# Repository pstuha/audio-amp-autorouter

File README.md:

# AmpRoute Studio 2.2.0

**Agent-first autorouter and 2-D board editor for LUT audio-amplifier PCBs.**

An AI agent invents a circuit and describes a board; AmpRoute turns it into a
DRC-clean, manufacturable PCB with Gerbers, a 1:1 toner-transfer template and
official CAM files. A human opens the same board in a familiar KiCad-like
editor. No KiCad plugin, no Python runtime, no external services.

---

## 60-second start

```powershell
cargo build --release           # target\release\amproute-studio.exe
.\target\release\amproute-studio.exe
```

GUI: **Open board…** → pick `.kicad_pcb` or JSON → **F5** → choose
**Export folder…** → **Ctrl+E**. No board is preloaded: the shipped amplifiers
are test fixtures, not presets.

Headless:

```powershell
# Route one of the five shipped test boards
.\amproute-studio.exe --cli --board lm386-mini -o out --json

# Route an agent-designed board
.\amproute-studio.exe --cli -i my_board.json -o out --json

# Two-layer variant with plated vias
.\amproute-studio.exe --cli -i my_board.json --two-layer -o out2 --json

# Official CAM formats (from KiCad's own exporters)
.\amproute-studio.exe --cli -i my_board.json --odb --ipc -o cam

# Machine-readable agent interface
cargo build --release --bin amproute-mcp
```

Exit codes: `0` success, `2` invalid board, `3` routing/export refused.

---

## What it does

| Stage | Implementation |
|-------|----------------|
| **Import** | `.kicad_pcb` and AmpRoute JSON; rotates footprints correctly; reports every skipped KiCad feature. |
| **Rules** | `R01`–`R11`: LUT feature band, vias, width, clearance, net class, acute corners, parallel runs, annular ring, drill, edge clearance. |
| **Placement** | Opt-in 180° footprint optimizer (`--optimize-placement`, MCP `optimize_placement`). |
| **Routing** | 8-connected/octile A* with exact-mm `Occupancy`, audio proximity penalties, star-ground and thermal zones, rip-up/reroute, line-of-sight simplification, 45° canonicalisation and LUT width taper. |
| **Verification** | Own audit + `kicad-cli pcb drc --severity-all`; 15 reference boards at 100 % routing with zero violations. |
| **Quality** | DC drop, I²R, IPC-2221 width, linear AC (MNA), EMI/crosstalk proxies, transient thermal — all versioned JSON. |
| **Export** | Gerber, SVG, PDF, 1:1 LUT template (front and mirrored back), `.kicad_pcb`, Excellon drill, IPC-2581 Rev C, ODB++ zip. |
| **Agents** | CLI `--json` (one document on stdout) and MCP JSON-RPC 2.0 over stdio. |

### Agent workflow

1. Agent creates a board (JSON or `.kicad_pcb`) — no GUI needed.
2. `route_board` validates, routes, audits and writes every deliverable.
3. `get_result` returns nets, DRC, measurements, quality verdict and exact file paths.
4. Human prints `lut_print.pdf` at 100 %, transfers toner, etches and solders.

Ten agent-designed boards are built in (`pam8403-mini`, `lm358-preamp`,
`tda2822-bridge`, `ne555-tone`, `classa-single`, `jfet-buffer`,
`discrete-opamp`, `lm1875-mono`, `ta2024-tripath`, `hybrid-output`) alongside
five shipped fixtures (`lm386-mini`, `tda2030-compact`, `cmoy-headphone`,
`classic-ltp`, `twin-pair-200`). All 15 route 100 % with KiCad DRC clean.

### Audio-specific routing

- Net classes set width, priority and routing cost (GND/PWR first, sensitive
  inputs short and direct).
- Input↔Power/Output proximity penalty ×10; Feedback↔Output/Power ×5.
- Star-ground bias (`board.rs::star_ground_point`) and thermal hotspot keep-outs.
- Single-layer LUT by default: vias forbidden, insulated-wire jumpers instead.
- Two-layer mode adds plated vias, B.Cu Gerber, mirrored B.Cu LUT sheet and drill.

---

## GUI

Familiar EDA layout: menu bar, toolbars, appearance/net/component tree, board
canvas, inspector, DRC and statistics, status bar.

- Zoom with the wheel, pan by drag, rotate with `R`/`Shift+R`, mirror with `F`.
- Click a pad, track, component or net to inspect it.
- Toggle layers, keep-outs and thermal heatmap.
- Statistics: board totals (copper, segments, routed nets), track-width min / avg / max,
  per-net table and thermal peak / average — **Copy stats** copies it to the clipboard.
- `F5` route, `Esc` stop, `Ctrl+O` open, `Ctrl+K` KiCad export, `Ctrl+E` all exports.
- Routing runs on a worker thread — the UI stays responsive.

---

## Machine interface

CLI `--json` prints exactly one `PipelineResult` JSON document; diagnostics go
to stderr. MCP server:

| Tool | Purpose |
|------|---------|
| `get_capabilities`, `get_quality_schema` | API version, formats, analysis schema |
| `list_boards`, `list_extra_boards` | Fixtures and agent designs |
| `validate_board`, `run_drc` | Pre-flight checks |
| `route_board`, `get_result` | Route, export and retrieve the full report |
| `run_ac`, `generate_netlist`, `run_emi`, `run_thermal` | Proxy analyses |
| `optimize_placement`, `set_lut_profile`, `suggest_jumpers` | Agent helpers |

Full contract: [`docs/agent-api.md`](docs/agent-api.md).

### Quality verdict

`quality` is separate from manufacturability. Hard gates: all nets routed,
rules clean, own DRC clean, KiCad DRC clean, exports written. Electrical,
AC, EMI and thermal verdicts gate `ok` only when the agent supplies data and
selects them through `analysis_policy`. All proxy reports carry `model`,
`confidence` and `assumptions`.

Honest verdicts: while currents are **assumed** (`assumed_currents: true`),
electrical violations (M02 track width vs IPC-2221, M03 drop) are advisory;
with real agent-supplied currents (`measure_currents`, `NetExcitation`) the
same violations gate `ok`. `assumed_currents: false` in every `get_result`.

History and comparisons: [`docs/quality-roadmap.md`](docs/quality-roadmap.md),
[`docs/router-roadmap.md`](docs/router-roadmap.md).

---

## Output files

| File | Purpose |
|------|---------|
| `board.gbr`, `board_b.gbr` | RS-274X copper layers, 4.6 format, millimetres |
| `board.svg` | Colour preview |
| `board.pdf` | Route report |
| `lut_print.pdf`, `lut_print_b.pdf` | 1:1 iron-on templates, front/mirrored back — print at 100 % |
| `<board>.kicad_pcb` | KiCad project board |
| `vias.drl` | Excellon drill for plated vias |
| `jumpers.csv` | Insulated-wire jumper endpoints |
| `board.xml` | IPC-2581 Rev C (KiCad exporter) |
| `board_odb.zip` | ODB++ (KiCad exporter) |

---

## Verification

```text
cargo test — 248 tests, 0 failures:
  215 unit + 5-board acceptance + 10-board acceptance
  e2e, MCP, reference, quality, standards, two-layer, SPICE golden

scripts\bench_validate.ps1 — routes all 15 boards, checks result.ok = true

kicad-cli pcb drc --severity-all   # 0 violations on all 15 boards
lm386-mini: 7/7 nets, non_canonical segments = 0
```

The golden SPICE test runs only when `AMPROUTE_NGSPICE` points to a simulator;
otherwise it skips. KiCad 10 is used automatically for DRC and optional CAM.

---

## Project layout

```
src/
  agent.rs, bin/amproute-mcp.rs   MCP/JSON agent interface
  board.rs, boards.rs             Model, net classes, fixtures and agent designs
  import.rs, sexpr.rs, kicad.rs   KiCad round-trip
  router.rs, routing_engine.rs    A*, octile search, rip-up, canonicalisation
  occupancy.rs, two_layer.rs      Exact clearance, layered completion
  preroute.rs, jumper.rs          Star power/ground, insulated-wire jumpers
  rules.rs, drc.rs                LUT rules and DRC
  measure.rs, ac.rs, emi.rs       DC/AC/EMI quality proxies
  thermal.rs                      2-D conduction + transient estimate
  export.rs                       Gerber/SVG/PDF/LUT/CAM
  gui.rs, main.rs                 egui editor and CLI
tests/                             Acceptance and contract tests
docs/                               Agent API and roadmaps
```

---

## Limitations

- Through-hole only; two-layer vias are supported in the tool but require a
  manufactured two-layer board.
- KiCad import is deliberately partial (no zones, teardrops or custom pads);
  skipped features are reported.
- Thermal is a 2-D/RC proxy, AC is linear MNA, EMI is geometric — none is a
  full-wave or FEM solver.
- Always verify scale/orientation in an independent Gerber viewer before fab.

---

## Bench validation

`scripts\bench_validate.ps1` routes all 15 boards and checks `result.ok`
(routability smoke — also used in CI).

**Bench validation of an amplifier is blocked — no physical bench is available
in this environment.** When a bench is available, the full procedure is:

1. **Routability smoke** — `scripts\bench_validate.ps1`: every board must print
   `OK` and exit 0. Reference: `lm386-mini` → 4 files, `drc=0`, `kicad_drc_ran=true`.
2. **Gain** — feed a 1 kHz sine (~0.1–1 Vpp) through the board's normal signal
   path (input pin → front-end net → output pad) with a function generator and
   a scope; compare with the board's class gain (net classes in the board JSON).
3. **THD** — same path, measured with a spectrum/FFT analyzer at a few levels
   (e.g., 0.1 / 1.0 × supply max); record %THD vs the class spec.
4. **Temperature** — run the board at max supply/output for a few minutes;
   measure with an IR camera or thermistor taps on the copper; keep the
   junction rise within the model's thermal limits.

Bench results become part of the record via `measure_currents` (then they
gate `ok`) or explicit `analysis_policy` — see
[`docs/agent-api.md`](docs/agent-api.md).

## Building

Rust 1.75+. On Linux install `libxkbcommon`, `libwayland-dev`, `libgl1-mesa-dev`.

```bash
cargo build --release
cargo test
```

## License

MIT — see [LICENSE](LICENSE).

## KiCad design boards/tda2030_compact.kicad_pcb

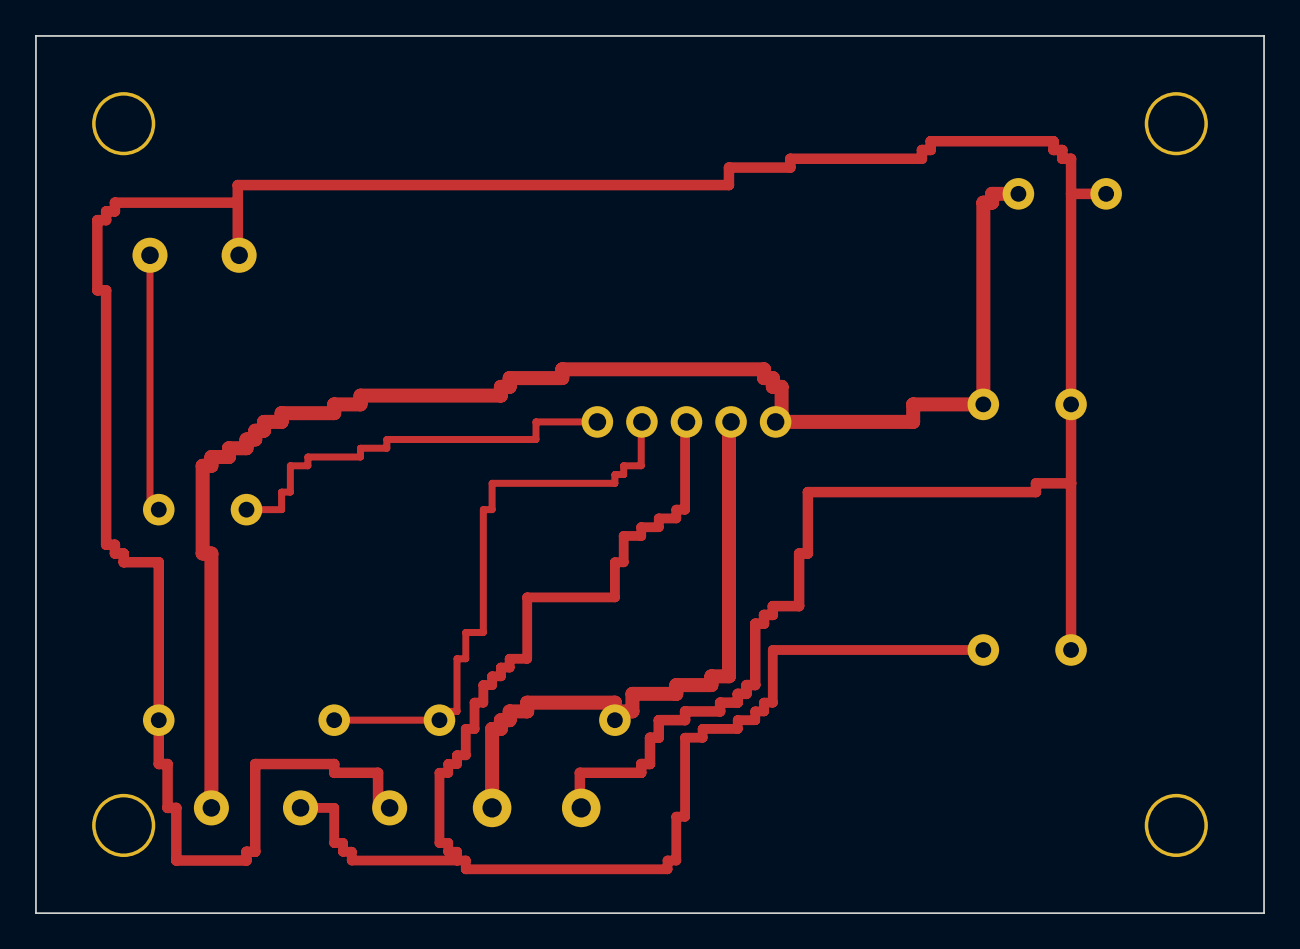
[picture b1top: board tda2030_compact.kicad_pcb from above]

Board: 2 copper layers, 70.0 x 50.0 mm, 14 parts (0 on the bottom side), 7 nets.

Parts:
C1: 2u2
C2: 100nF
C3, C4: 2200uF
H1, H2, H3, H4: MountingHole; MountingHole_3.2mm
J1: RCA-IN
J2: PWR
J3: SPK
R1: 22k
R2: 680R
U1: TDA2030

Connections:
FB: R1.1, R2.2, U1.2
GND: C2.2, C3.2, C4.2, J1.2, J2.3, J3.2, R2.1
IN: C1.1, J1.1
IN_AC: C1.2, U1.1
OUT: J3.1, R1.2, U1.4
V+: C2.1, C3.1, J2.1, U1.5
V-: C4.1, J2.2, U1.3

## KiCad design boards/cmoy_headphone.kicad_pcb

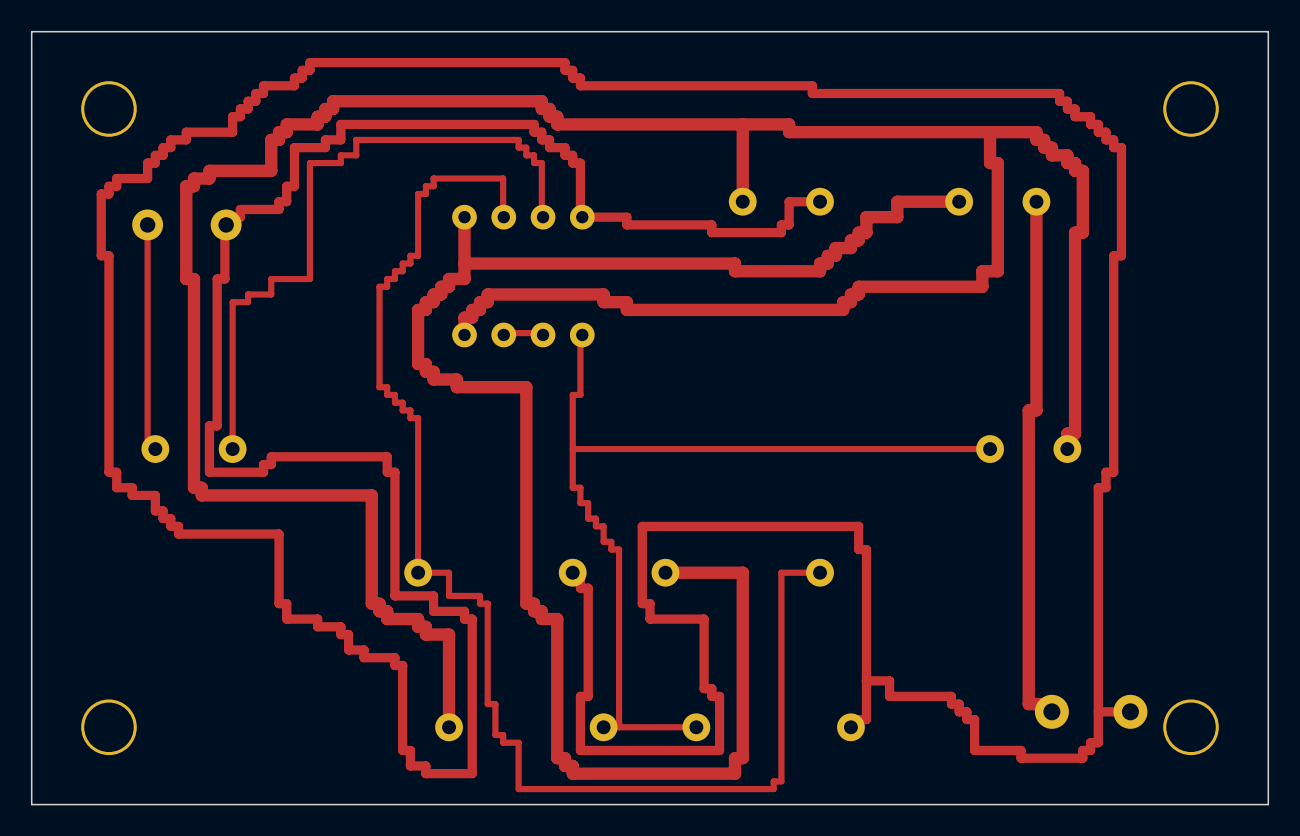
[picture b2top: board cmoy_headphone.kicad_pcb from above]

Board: 2 copper layers, 80.0 x 50.0 mm, 15 parts (0 on the bottom side), 9 nets.

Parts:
C1: 1uF
C2: 470uF
C3: 100uF
C4: 10uF
H1, H2, H3, H4: MountingHole; MountingHole_3.2mm
J1: RCA-IN
J2: SPK
R1, R3, R4: 10k
R2: 47k
U1: NE5532

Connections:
AMP_OUT: C2.1, R2.1, U1.1
FB: R1.1, R2.2, U1.2
GND: C4.2, J1.2, J2.2, R1.2, R4.2, U1.4
IN: C1.1, J1.1
IN_AC: C1.2, U1.3
PHONES: C2.2, J2.1
SPARE: U1.6, U1.7
V+: C3.2, C4.1, R3.1, U1.8
VGND: C3.1, R3.2, R4.1, U1.5

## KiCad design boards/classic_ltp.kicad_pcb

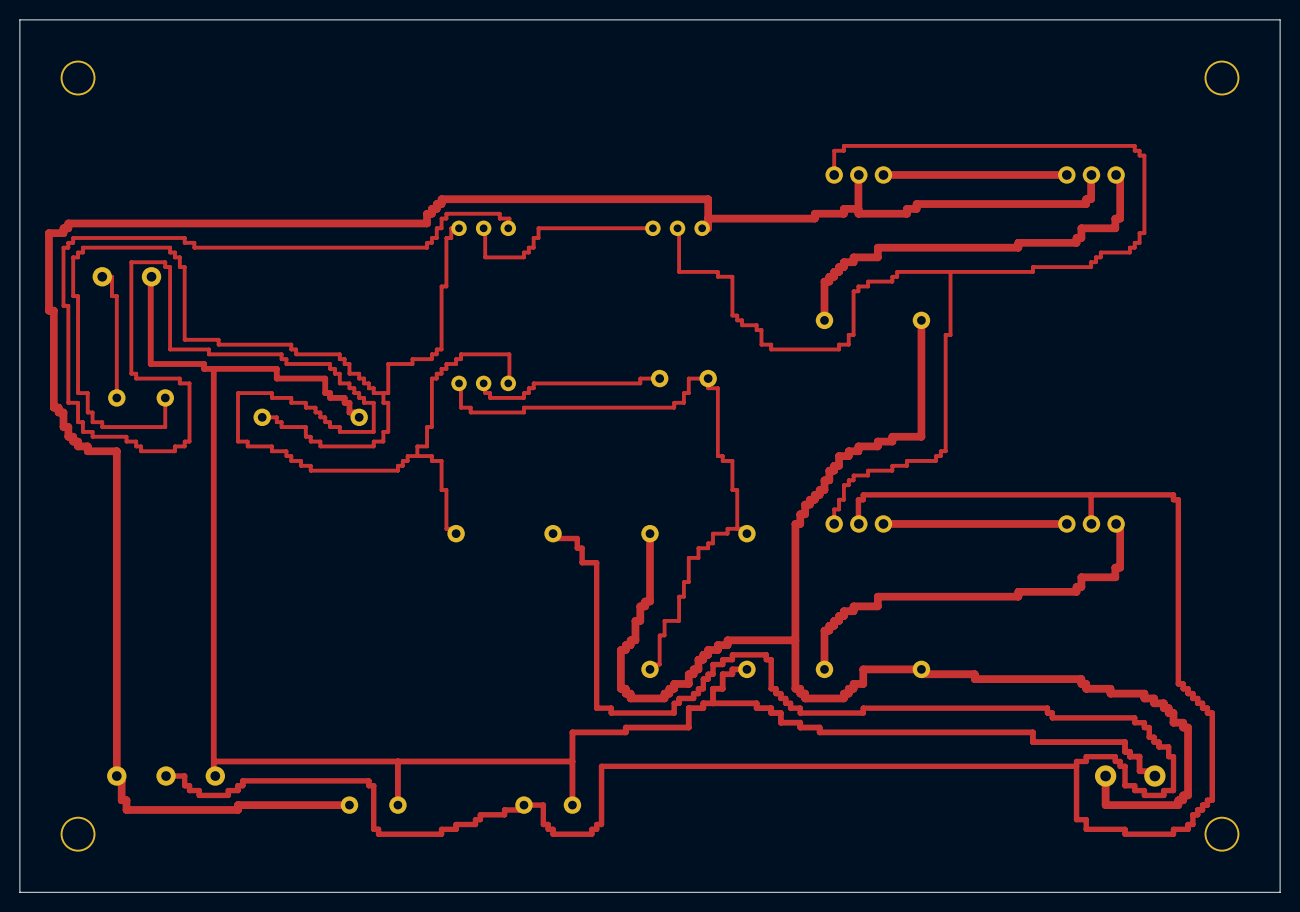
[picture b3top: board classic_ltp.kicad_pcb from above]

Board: 2 copper layers, 130.0 x 90.0 mm, 24 parts (0 on the bottom side), 15 nets.

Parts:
C1: 4u7
C2: 47pF
C3, C4: 4700uF
H1, H2, H3, H4: MountingHole; MountingHole_3.2mm
J1: RCA-IN
J2: PWR
J3: SPK
Q1, Q2: K170
Q3: K310
Q4: TIP41C
Q5: TIP42C
Q6: 2N3055
Q7: MJE2955
R1: 100k
R2, R5: 22k
R3, R4: 0R47
R6: 1k

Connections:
DRV_N: Q4.3, Q6.1
DRV_P: Q5.3, Q7.1
E_N: Q6.3, R3.1
E_P: Q7.3, R4.1
FB: C2.2, Q2.1, R5.2, R6.1
GND: C3.2, C4.2, J1.2, J2.3, J3.2, R1.2, R6.2
IN: C1.1, J1.1
IN_AC: C1.2, Q1.1, R1.1
LTP_A: Q1.2, Q3.1
LTP_B: C2.1, Q2.2
SPK: J3.1, R3.2, R4.2, R5.1
TAIL: Q1.3, Q2.3, R2.1
V+: C3.1, J2.1, Q3.3, Q4.2, Q6.2
V-: C4.1, J2.2, Q5.2, Q7.2, R2.2
VAS_OUT: Q3.2, Q4.1, Q5.1

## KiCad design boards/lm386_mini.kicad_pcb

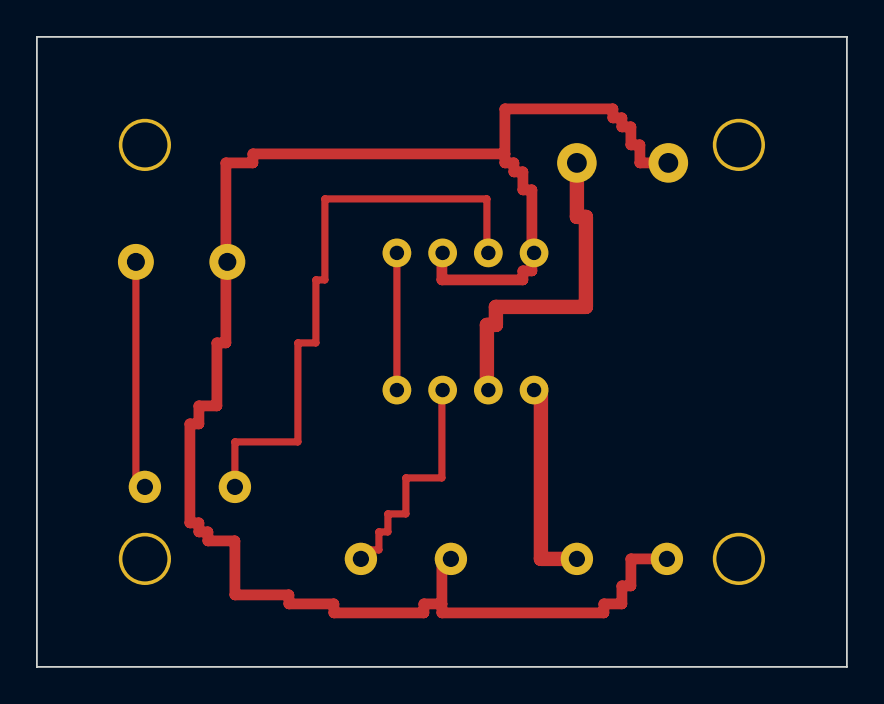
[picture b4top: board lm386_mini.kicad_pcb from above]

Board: 2 copper layers, 45.0 x 35.0 mm, 10 parts (0 on the bottom side), 7 nets.

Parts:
C1: 100nF
C2: 10uF
C3: 100uF
H1, H2, H3, H4: MountingHole; MountingHole_2.5mm
J1: RCA-IN
J2: SPK
U1: LM386

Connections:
BYPASS: C2.1, U1.7
GAIN: U1.1, U1.8
GND: C2.2, C3.2, J1.2, J2.2, U1.2, U1.4
IN: C1.1, J1.1
IN_AC: C1.2, U1.3
OUT: J2.1, U1.6
V+: C3.1, U1.5

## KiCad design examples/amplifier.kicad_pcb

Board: 0 copper layers, 6 parts (0 on the bottom side), 5 nets, no tracks yet.

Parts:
C1: 100nF; C_Disc_D5.0mm_W2.5mm_P5.00mm
J1: IN; PinHeader_1x02_P2.54mm_Vertical
J2: OUT; PinHeader_1x02_P2.54mm_Vertical
R1: 1k; R_Axial_DIN0207_L6.3mm_D2.5mm_P10.16mm_Horizontal
R2: 10k; R_Axial_DIN0207_L6.3mm_D2.5mm_P10.16mm_Horizontal
U1: LM1875; TO-220-3_Vertical

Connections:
GND: C1.2, J1.2, J2.2
IN: J1.1, R1.1
MID: R1.2, R2.1, U1.1
OUT: J2.1, U1.3
VCC: C1.1, U1.2
